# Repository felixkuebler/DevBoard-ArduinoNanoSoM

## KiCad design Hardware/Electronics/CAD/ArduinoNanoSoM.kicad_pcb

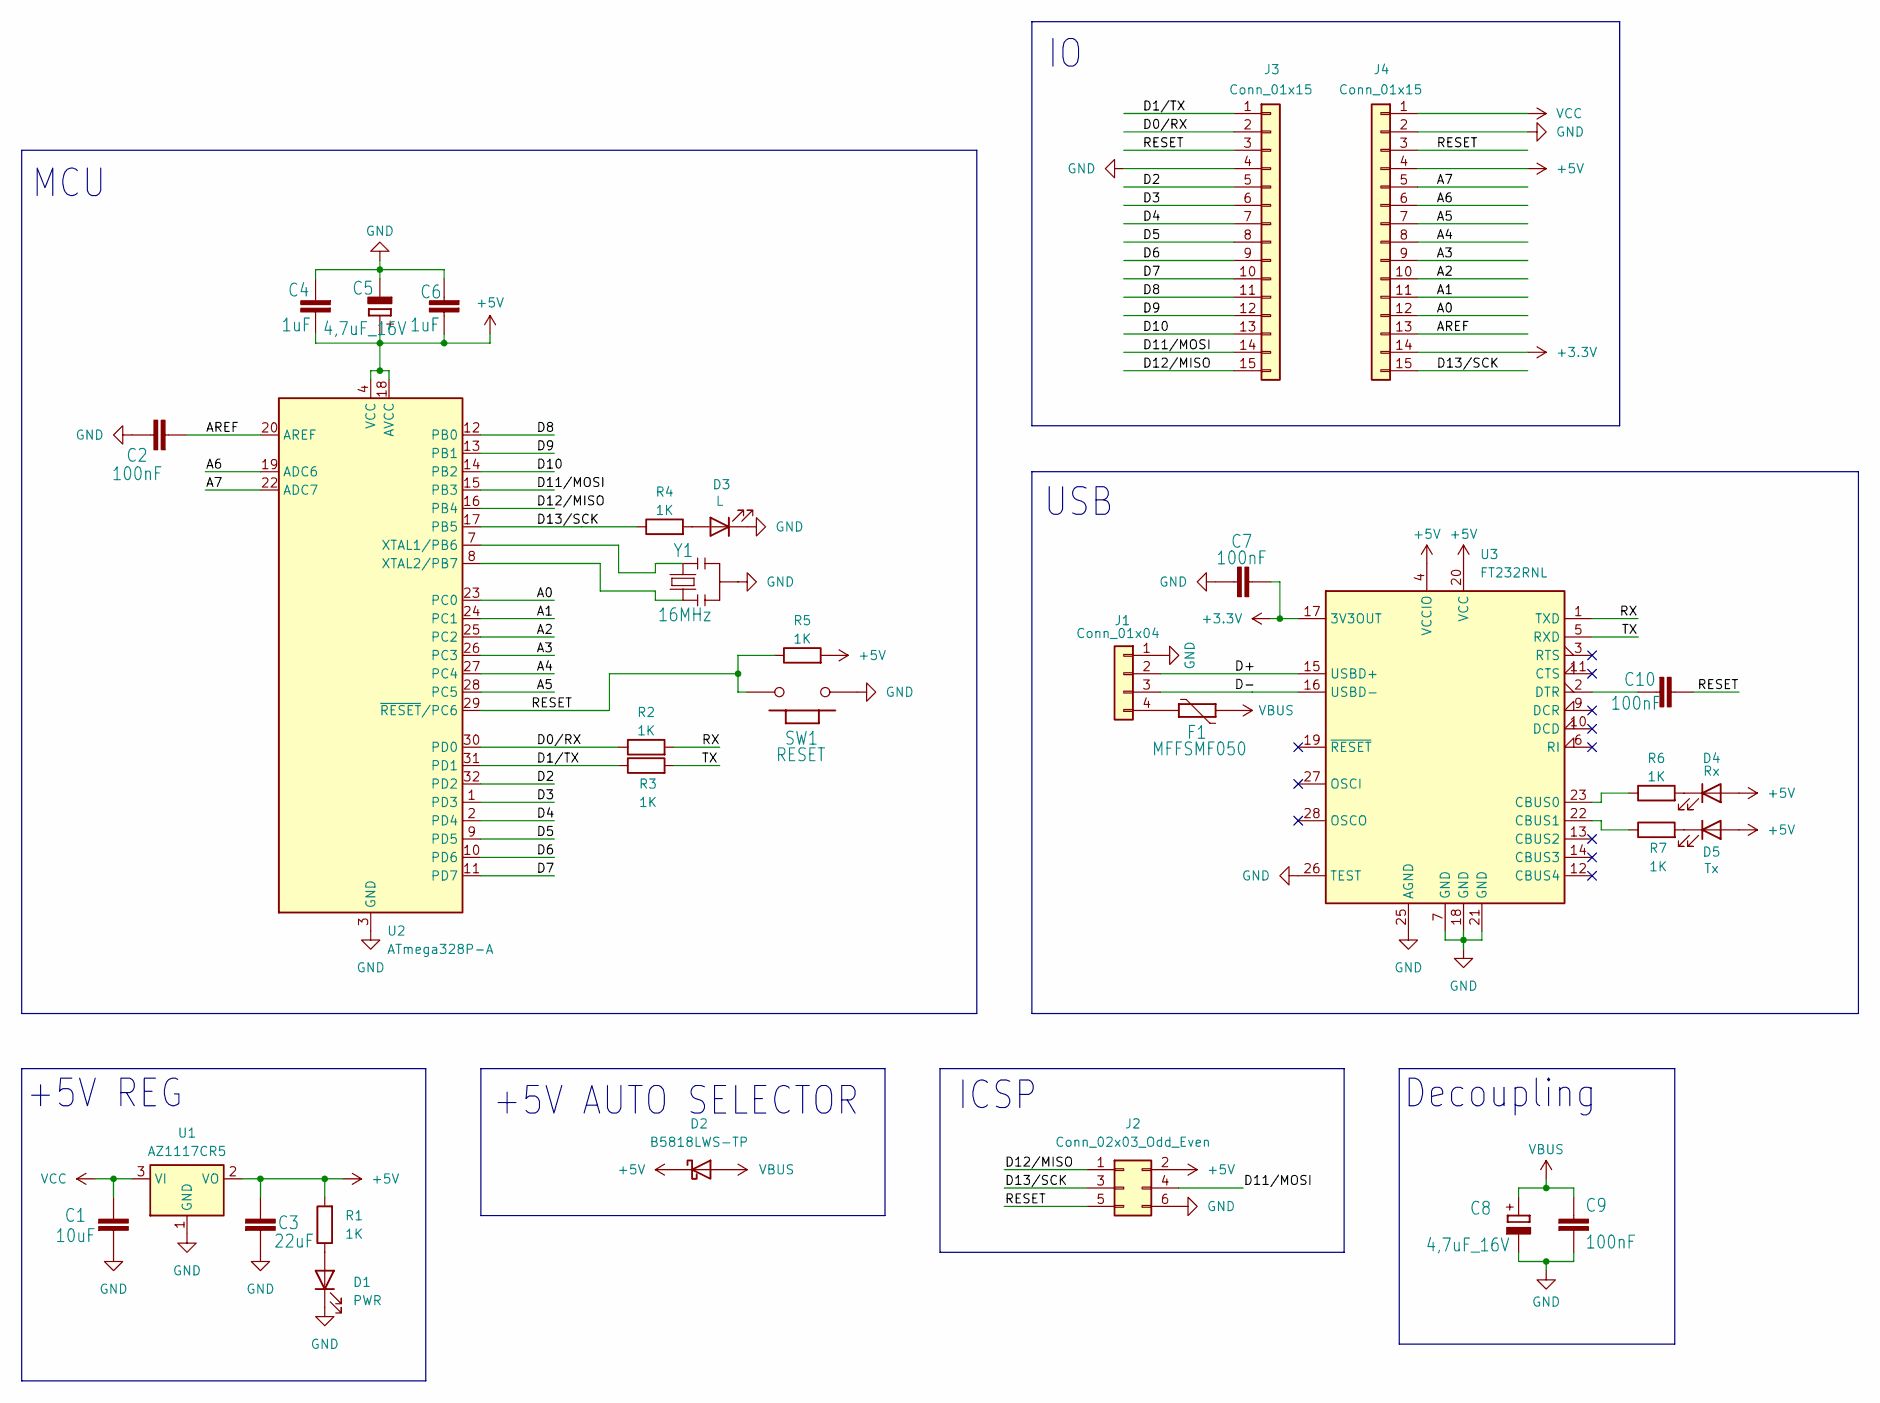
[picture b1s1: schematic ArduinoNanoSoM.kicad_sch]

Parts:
C1: 10uF; C_0402_1005Metric
C2, C7, C9, C10: 100nF; C_0402_1005Metric
C3: 22uF; C_0402_1005Metric
C4, C6: 1uF; C_0402_1005Metric
C5, C8: 4,7uF_16V; C_0402_1005Metric
D1: PWR; D_0402_1005Metric
D2: B5818LWS-TP; D_SOD-323
D3: L; D_0402_1005Metric
D4: Rx; D_0402_1005Metric
D5: Tx; D_0402_1005Metric
F1: MFFSMF050; Fuse_0603_1608Metric
J1: Conn_01x04; PinHeader_1x04_P2.54mm_Castellated
J2: Conn_02x03_Odd_Even; PinHeader_2x03_P2.54mm_Vertical
J3, J4: Conn_01x15; PinHeader_1x15_P2.54mm_Castellated
R1, R2, R3, R4, R5, R6, R7: 1K; R_0402_1005Metric
SW1: RESET; SW_Push_SPST_NO_Alps_SKRK
U1: AZ1117CR5; SOT-89-3
U2: ATmega328P-A; TQFP-32_7x7mm_P0.8mm
U3: FT232RNL; SSOP-28_5.3x10.2mm_P0.65mm
Y1: 16MHz; Resonator_SMD_Murata_CSTxExxV-3Pin_3.0x1.1mm

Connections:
+3.3V: C7.2, J4.14, U3.17 (3V3OUT)
+5V: C3.1, C4.1, C5.1 (+), C6.1, D2.1 (K), D4.2 (A), D5.2 (A), J2.2, J4.4, R1.2, R5.2, U1.2 (VO), U2.4 (VCC), U2.6 (VCC), U2.18 (AVCC), U3.4 (VCCIO), U3.20 (VCC)
/A0: J4.12, U2.23 (PC0)
/A1: J4.11, U2.24 (PC1)
/A2: J4.10, U2.25 (PC2)
/A3: J4.9, U2.26 (PC3)
/A4: J4.8, U2.27 (PC4)
/A5: J4.7, U2.28 (PC5)
/A6: J4.6, U2.19 (ADC6)
/A7: J4.5, U2.22 (ADC7)
/AREF: C2.2, J4.13, U2.20 (AREF)
/D0/RX: J3.2, R2.1, U2.30 (PD0)
/D1/TX: J3.1, R3.1, U2.31 (PD1)
/D2: J3.5, U2.32 (PD2)
/D3: J3.6, U2.1 (PD3)
/D4: J3.7, U2.2 (PD4)
/D5: J3.8, U2.9 (PD5)
/D6: J3.9, U2.10 (PD6)
/D7: J3.10, U2.11 (PD7)
/D8: J3.11, U2.12 (PB0)
/D9: J3.12, U2.13 (PB1)
/D10: J3.13, U2.14 (PB2)
/D11/MOSI: J2.4, J3.14, U2.15 (PB3)
/D12/MISO: J2.1, J3.15, U2.16 (PB4)
/D13/SCK: J2.3, J4.15, R4.1, U2.17 (PB5)
/D+: J1.2, U3.15 (USBD+)
/D-: J1.3, U3.16 (USBD-)
/RESET: C10.1, J2.5, J3.3, J4.3, R5.1, SW1.2, U2.29 (~RESET/PC6)
/RX: R2.2, U3.1 (TXD)
/TX: R3.2, U3.5 (RXD)
GND: C1.2, C2.1, C3.2, C4.2, C5.2 (-), C6.2, C7.1, C8.2 (-), C9.2, D1.1 (K), D3.1 (K), J1.1, J2.6, J3.4, J4.2, SW1.1, U1.1 (GND), U2.3 (GND), U2.5 (GND), U2.21 (GND), U3.7 (GND), U3.18 (GND), U3.21 (GND), U3.25 (AGND), U3.26 (TEST), Y1.2
unnamed: D1.2 (A), R1.1
unnamed: D3.2 (A), R4.2
unnamed: D4.1 (K), R6.2
unnamed: D5.1 (K), R7.2
unnamed: F1.2, J1.4
unnamed: U2.7 (XTAL1/PB6), Y1.1
unnamed: U2.8 (XTAL2/PB7), Y1.3
unnamed: R6.1, U3.23 (CBUS0)
unnamed: R7.1, U3.22 (CBUS1)
unnamed: C10.2, U3.2 (DTR)
VBUS: C8.1 (+), C9.1, D2.2 (A), F1.1
VCC: C1.1, J4.1, U1.3 (VI)

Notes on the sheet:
MCU
+5V AUTO SELECTOR
USB
Decoupling
ICSP
+5V REG

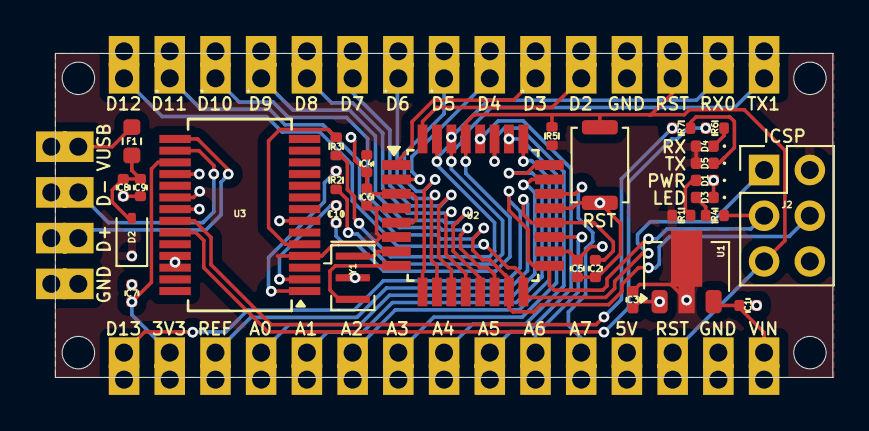
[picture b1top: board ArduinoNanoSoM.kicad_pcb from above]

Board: 4 copper layers, 43.2 x 18.0 mm, 33 parts (1 on the bottom side), 43 nets.

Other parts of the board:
FRAME1: DNP; FRAME

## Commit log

2025-01-28 Version 1.0 of Arduino Nano SoM
